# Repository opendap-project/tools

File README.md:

# tools

| Folder | Content |
| --- | --- |
| [`hardware/`](hardware/README.md) | The hardware tools' Python project, and the [component export contract](hardware/docs/specs/component-export.md) every component follows |
| [`hooks/`](hooks/README.md) | Shared [pre-commit](https://pre-commit.com) hooks for every OpenDAP repository |
| [`host/`](host/README.md) | Developer host setup for OpenDAP: the tools, toolchains and checks every contributor installs |
| [`image/`](image/README.md) | Tools to build Blackbird OS images and the software that goes into them, for the platform's maintainers |
| [`core/`](core/README.md) | What every domain shares: command-line conventions and their conformance test, the evaluation-matrix engine, the `odw` package's shared modules |
| [`documentation/`](documentation/README.md) | The documentation engines: requirements as data, docs gates and index, RFC status, verification matrices |
| [`schemas/`](schemas/README.md) | The workspace formats as JSON Schemas, with their fixtures and tests |
| [`parts/`](parts/README.md) | Part data: the sourcing evaluation matrix (`odw parts`) and the part file sync |
| [`sim/`](sim/README.md) | The study runner: a board's simulation regression checks (`odw sim`) |
| [`electronics/`](electronics/README.md) | Electronics tooling: PCB and schematic craft checks, the layer stack and impedance solver, board variants |
| [`env/`](env/README.md) | The maintainers' host environment: QEMU for virtual devices, a LAN address for them, the build VM, the indexer |
| [`workspace/`](workspace/README.md) | `odw` itself and the workspace tools: plan, audit, shared files, the restructure's cut engine |
| [`mechanical/`](mechanical/README.md) | Mechanical tooling: the FreeCAD export and `odw render`'s CAD adapters |
| [`measure/`](measure/README.md) | Measurement tooling for OpenDAP: motion recorded on screen and measured (`odw motion`) |
| [`verify/`](verify/README.md) | Verification tooling for OpenDAP: simulations and samples captured from sessions, on the virtual T1 now and on prototypes later |

Each folder keeps its own `README.md`, `CLAUDE.md` and `REUSE.toml`; the licence texts are in `LICENSES/`. `hardware/`, `hooks/`, `host/`, `image/` and `verify/` came from the former `toolkit-hardware`, `toolkit-hooks`, `toolkit-host`, `toolkit-image` and `toolkit-verify` repositories with their history ([RFC 0017](https://github.com/opendap-project/rfcs/blob/main/text/0017-naming-and-topology.md)); their content moves into the domain folders one domain at a time (`core/`, `documentation/`, `electronics/`, `env/`, `measure/`, `mechanical/`, `parts/`, `schemas/`, `sim/` and `workspace/` so far).

## Tests never inherit a hook's git variables

Under a pre-commit hook, git exports `GIT_DIR`, `GIT_INDEX_FILE` and others. A test that runs git (a fixture repository, `git init`, a tool that calls git) with them acts on the repository being committed: it has set `core.bare` and written a placeholder identity there. Every test file that starts a process removes every `GIT_*` variable first, one way per language:

| Tests | Protection |
| --- | --- |
| Python under pytest (every suite the root's `pyproject.toml` runs, `core/tests`, `core/component/tests`, `documentation/tests`, `env/tests`, `schemas/tests` and `workspace/tests`) | the autouse fixture in the root's `conftest.py`, which applies to every test below it |
| Python under unittest (`electronics/`, `hardware/`, `hooks/`, `image/`, `measure/`, `parts/`, `sim/`) | at the top of each test module, after its imports: `for _k in [k for k in os.environ if k.startswith("GIT_")]: del os.environ[_k]` (in the module, because `python3 -m unittest discover tests` never imports `tests/__init__.py`) |
| Rust (`workspace/crates/odw-dispatch/tests/odw.rs`) | the `command()` helper, which starts every child from `env_clear()`; a helper that only drops git's variables calls `env_remove` for each `GIT_*` one |
| Shell (`image/tests/cli.sh`, `measure/tests/cli.sh`) | after `set -u`: `for v in $(env \| sed -n 's/^\(GIT_[A-Za-z0-9_]*\)=.*/\1/p'); do unset "$v"; done` |

The other direction holds too: a tool that commits (`odw rename`) runs git in the environment a plain `git commit` has (`audit.hook_env`), never its own runtime, so the hooks' tests do not run with its virtual environment first on `PATH` (its `python3`, with `odw` installed) or the folder variables the dispatcher exports (HL-109).

`odw audit` lists, per repository, the test files that run git without one of these (`tests_running_git_unprotected`). A `conftest.py` beside a `pyproject.toml` counts only for that project's pytest `testpaths`, so a unittest module elsewhere still needs its own stanza. `core/tests/git-leak.sh DIR COMMAND…` runs a suite with `GIT_DIR` and `GIT_INDEX_FILE` pointing at a scratch repository and fails if the suite changed it.

## License

This repository follows the [REUSE](https://reuse.software) layout: licence texts in `LICENSES/`, and each folder's `REUSE.toml` maps its paths. Copyright © 2026 The OpenDAP Project.

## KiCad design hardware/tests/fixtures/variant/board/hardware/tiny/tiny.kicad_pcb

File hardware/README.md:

# Toolkit hardware

What is left of the former toolkit-hardware: the [component export contract](docs/specs/component-export.md) every component follows, kept at its published path until the link pass, and the hardware tools' Python project.

Its tools moved into the tools root's domain folders (HL-71): the craft checks, `odw stackup` and `odw variant` to [`electronics/`](../electronics/README.md), `odw sim` to [`sim/`](../sim/README.md), `odw parts` to [`parts/`](../parts/README.md), `odw component`, `odw render`, `clihost.py` and the KiCad S-expression model to [`core/`](../core/README.md), and the FreeCAD export to [`mechanical/`](../mechanical/README.md).

## Layout

- `tools/pyproject.toml`, `tools/uv.lock` — the Python dependencies of `odw stackup`, `odw component` and the craft rules' schema test (numpy, scipy, scikit-fem, pyyaml, jsonschema), hash-locked, until the one Python workspace at the root
- `docs/` — requirements and the component export contract

## License

This folder follows the [REUSE](https://reuse.software) layout: license texts live in the root's `LICENSES/` and `REUSE.toml` maps each path to its license.

- Default: **GNU GPL v3.0 or later** (`GPL-3.0-or-later`)
- Markdown files and `docs/`: **Creative Commons Attribution-ShareAlike 4.0** (`CC-BY-SA-4.0`)

Copyright © 2026 The OpenDAP Project.

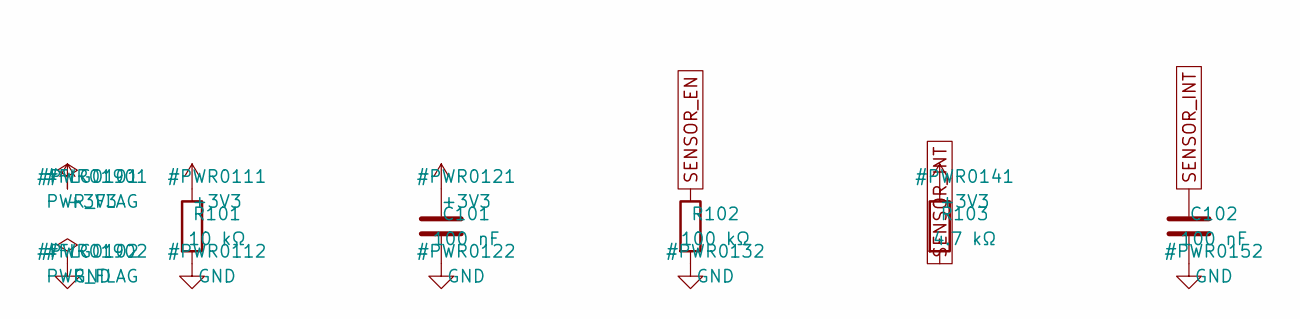
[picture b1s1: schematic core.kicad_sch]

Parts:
C101, C102: 100 nF; C_0402_1005Metric; MPN GRM155R71C104KA88D
R101: 10 kΩ; R_0603_1608Metric; MPN RC0603FR-0710KL
R102: 100 kΩ; R_0603_1608Metric; MPN RC0603FR-07100KL
R103: 4.7 kΩ; R_0603_1608Metric; MPN RC0603FR-074K7L

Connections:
+3V3: C101.1, R101.1, R103.1; also elsewhere on the board
GND: C101.2, C102.2, R101.2, R102.2; also elsewhere on the board
SENSOR_EN: R102.1; also elsewhere on the board
SENSOR_INT: C102.1, R103.2; also elsewhere on the board

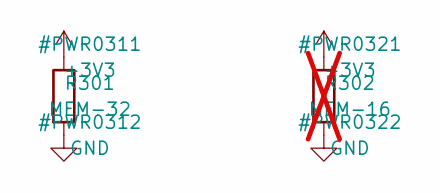
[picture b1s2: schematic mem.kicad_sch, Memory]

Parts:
R301: MEM-32; R_0603_1608Metric; MPN MEM32-X
R302: MEM-16; R_0603_1608Metric; MPN MEM16-Y; not fitted

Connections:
+3V3: R301.1, R302.1; also elsewhere on the board
GND: R301.2, R302.2; also elsewhere on the board

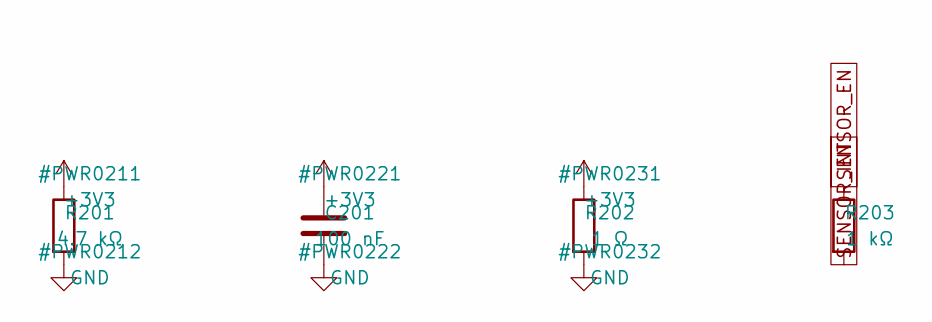
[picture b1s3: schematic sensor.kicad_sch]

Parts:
C201: 100 nF; C_0402_1005Metric; MPN GRM155R71C104KA88D
R201: 4.7 kΩ; R_0603_1608Metric; MPN RC0603FR-074K7L
R202: 1 Ω; R_0603_1608Metric; MPN RL0603FR-7W1RL
R203: 1 kΩ; R_0603_1608Metric; MPN RC0603FR-071KL

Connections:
+3V3: C201.1, R201.1, R202.1; also elsewhere on the board
GND: C201.2, R201.2, R202.2; also elsewhere on the board
SENSOR_EN: R203.1; also elsewhere on the board
SENSOR_INT: R203.2; also elsewhere on the board

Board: 2 copper layers, 11 parts (0 on the bottom side), 4 nets, no tracks yet.
